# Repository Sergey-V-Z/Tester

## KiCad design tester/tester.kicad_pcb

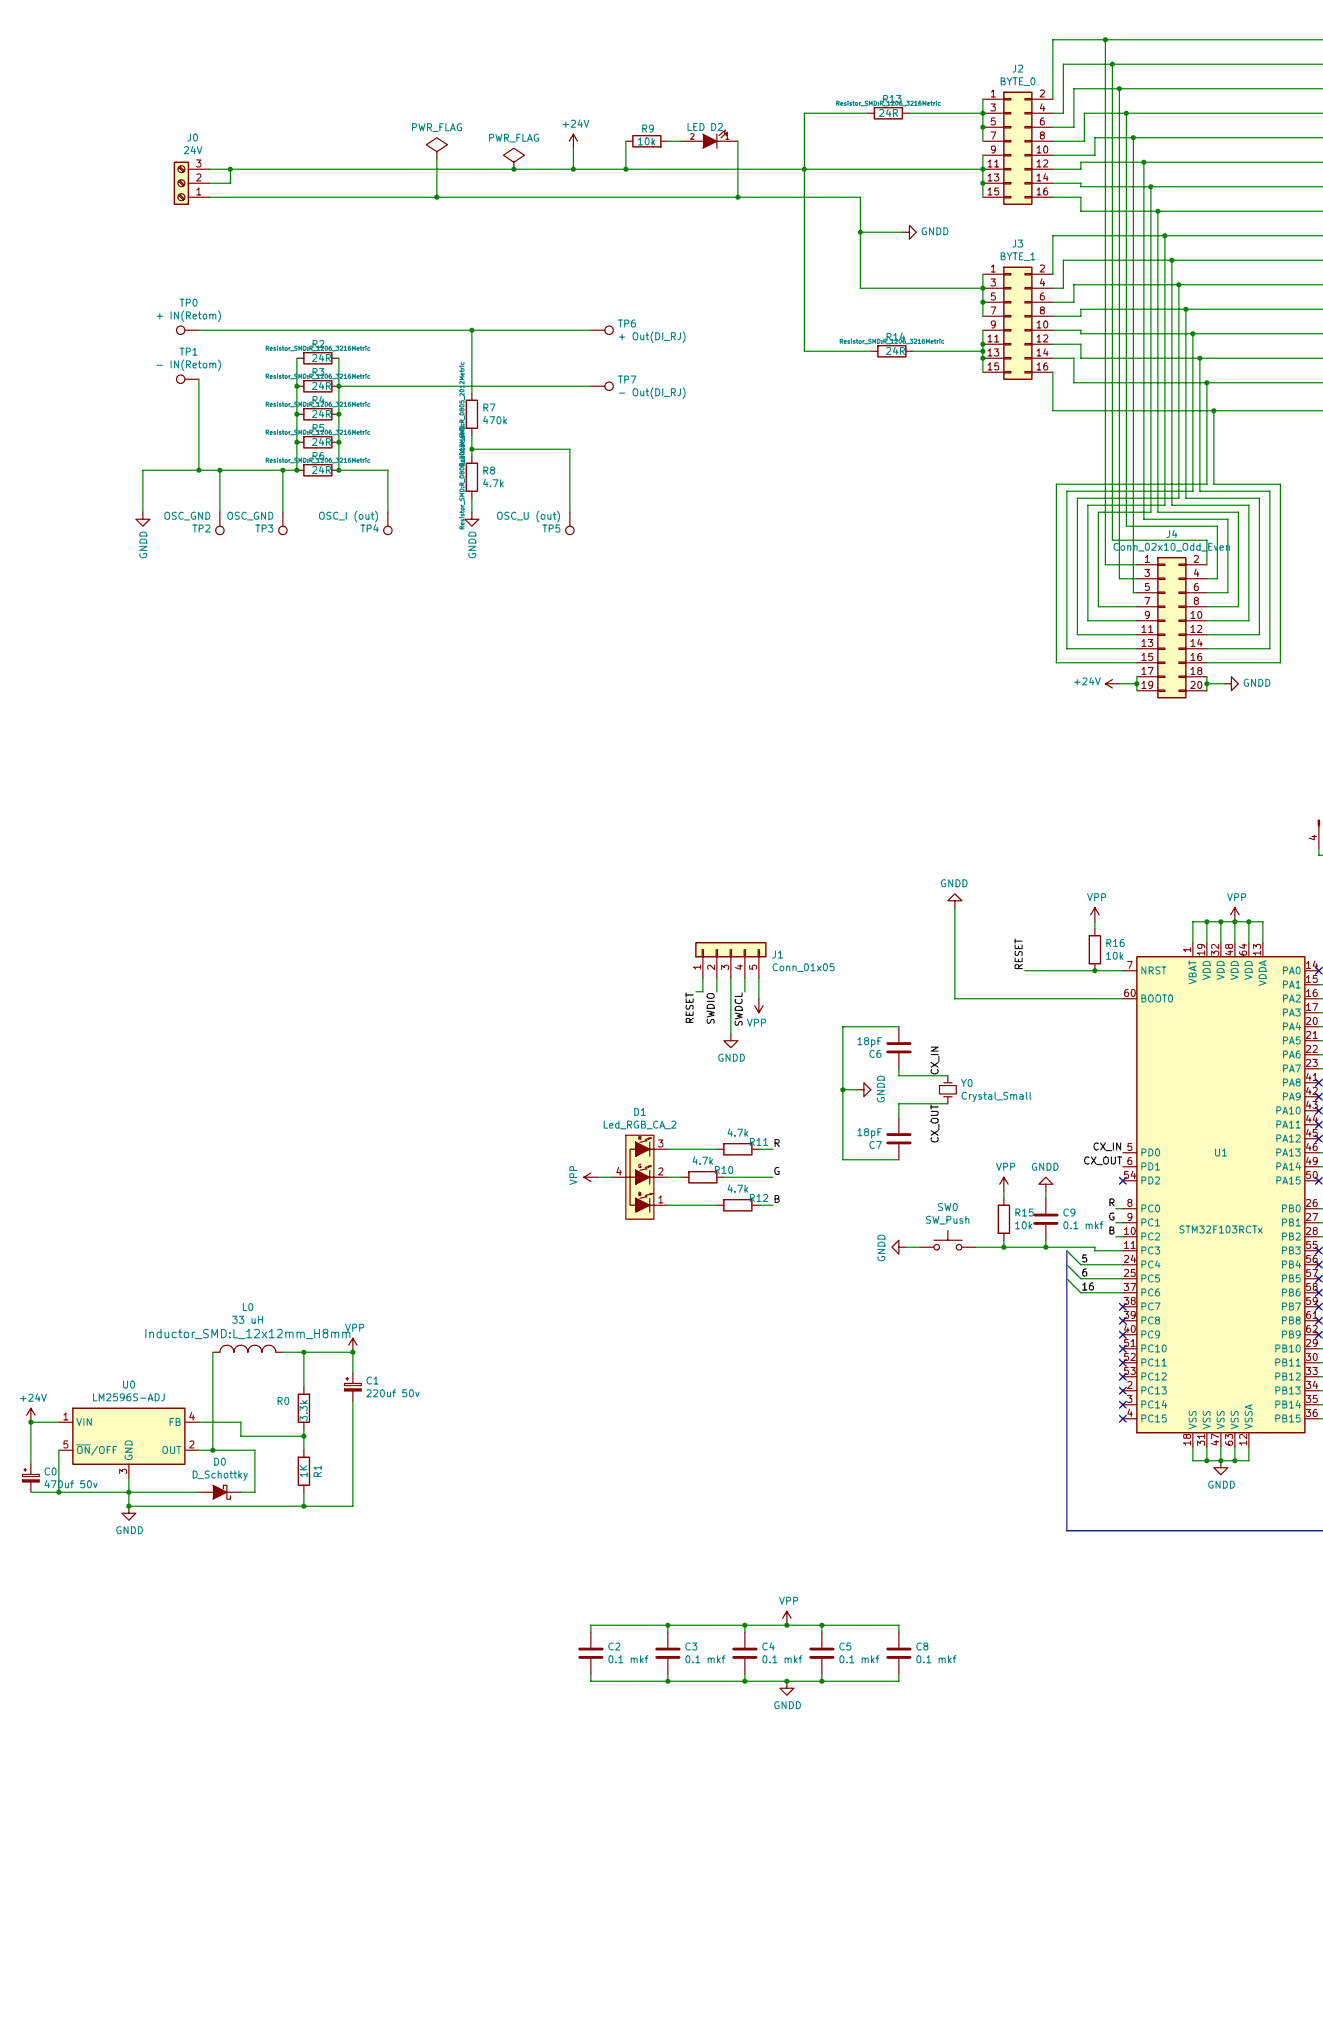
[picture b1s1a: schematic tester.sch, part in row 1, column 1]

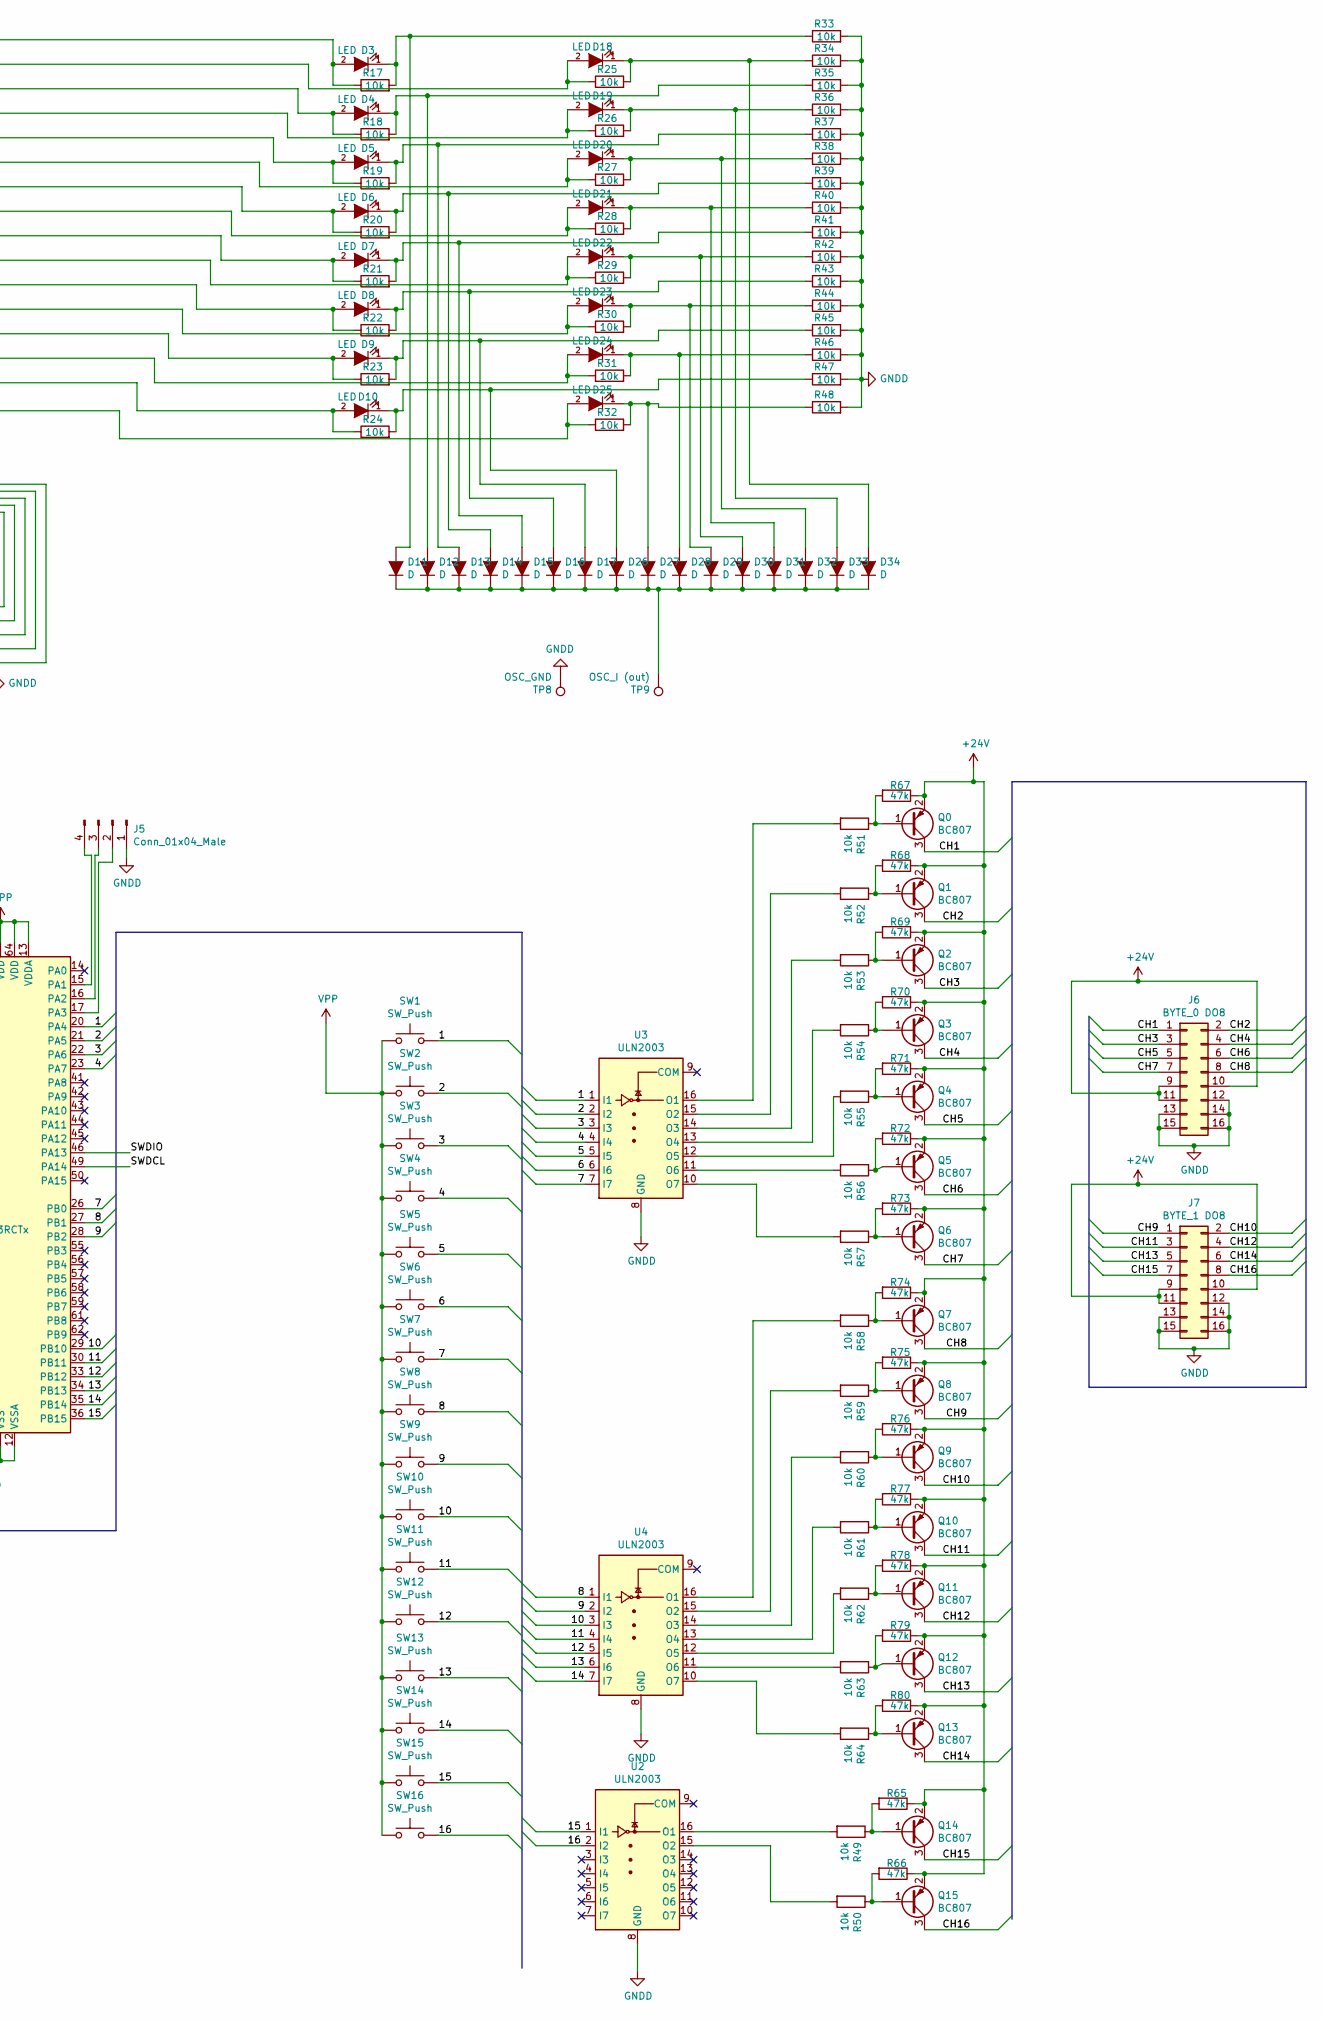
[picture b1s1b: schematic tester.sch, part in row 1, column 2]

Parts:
C0: 470uf 50v; CP_Radial_D10.0mm_P5.00mm
C1: 220uf 50v; CP_Radial_D10.0mm_P5.00mm
C2, C3, C4, C5, C8, C9: 0.1 mkf; C_0603_1608Metric_Pad1.05x0.95mm_HandSolder
C6, C7: 18pF; C_0603_1608Metric
D0: D_Schottky; D_SMC
D1: Led_RGB_CA_2; LED_Avago_PLCC4_3.2x2.8mm_CW
D2, D3, D4, D5, D6, D7, D8, D9, D10, D18, D19, D20, D21, D22, D23, D24, D25: LED; D_0805_2012Metric
D11, D12, D13, D14, D15, D16, D17, D26, D27, D28, D29, D30, D31, D32, D33, D34: D; D_SMB_Handsoldering
J0: 24V; TerminalBlock_bornier-3_P5.08mm
J1: Conn_01x05; PinHeader_1x05_P2.54mm_Vertical
J2: BYTE_0; IDC-Header_2x08_P2.54mm_Vertical
J3: BYTE_1; IDC-Header_2x08_P2.54mm_Vertical
J4: Conn_02x10_Odd_Even; IDC-Header_2x10_P2.54mm_Vertical
J5: Conn_01x04_Male; PinSocket_1x04_P2.54mm_Vertical
J6: BYTE_0 DO8; IDC-Header_2x08_P2.54mm_Vertical
J7: BYTE_1 DO8; IDC-Header_2x08_P2.54mm_Vertical
L0: 33 uH; L_12x12mm_H8mm
Q0, Q1, Q2, Q3, Q4, Q5, Q6, Q7, Q8, Q9, Q10, Q11, Q12, Q13, Q14, Q15: BC807; SOT-23
R0: 3.3k; R_0805_2012Metric_Pad1.15x1.40mm_HandSolder
R1: 1K; R_0805_2012Metric
R2, R3, R4, R5, R6, R13, R14: 24R; R_1206_3216Metric
R7: 470k; R_0805_2012Metric
R8: 4.7k; R_0805_2012Metric
R9, R17, R18, R19, R20, R21, R22, R23, R24, R25, R26, R27, R28, R29, R30, R31, R32, R33, R34, R35, R36, R37, R38, R39, R40, R41, R42, R43, R44, R45, R46, R47, R48: 10k; R_0805_2012Metric
R10, R11, R12: 4.7k; R_0805_2012Metric_Pad1.15x1.40mm_HandSolder
R15, R16, R49, R50, R51, R52, R53, R54, R55, R56, R57, R58, R59, R60, R61, R62, R63, R64: 10k; R_0805_2012Metric_Pad1.15x1.40mm_HandSolder
R65, R66, R67, R68, R69, R70, R71, R72, R73, R74, R75, R76, R77, R78, R79, R80: 47k; R_0805_2012Metric_Pad1.15x1.40mm_HandSolder
SW0, SW1, SW2, SW3, SW4, SW5, SW6, SW7, SW8, SW9, SW10, SW11, SW12, SW13, SW14, SW15, SW16: SW_Push; SW_PUSH_6mm
TP0: + IN(Retom); TestPoint_Plated_Hole_D3.0mm
TP1: - IN(Retom); TestPoint_Plated_Hole_D3.0mm
TP2, TP3, TP8: OSC_GND; TestPoint_Loop_D2.60mm_Drill0.9mm_Beaded
TP4, TP9: OSC_I (out); TestPoint_Loop_D2.60mm_Drill0.9mm_Beaded
TP5: OSC_U (out); TestPoint_Loop_D2.60mm_Drill0.9mm_Beaded
TP6: + Out(DI_RJ); TestPoint_Plated_Hole_D3.0mm
TP7: - Out(DI_RJ); TestPoint_Plated_Hole_D3.0mm
U0: LM2596S-ADJ; TO-263-5_TabPin3
U1: STM32F103RCTx; LQFP-64_10x10mm_P0.5mm
U2, U3, U4: ULN2003; SOIC-16_3.9x9.9mm_P1.27mm
Y0: Crystal_Small; Crystal_SMD_HC49-SD

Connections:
+24V: C0.1, J0.2, J0.3, J2.9, J2.11, J2.13, J2.15, J4.17, J4.19, J6.9, J6.10, J6.11, J7.9, J7.10, J7.11, Q0.2 (E), Q1.2 (E), Q2.2 (E), Q3.2 (E), Q4.2 (E), Q5.2 (E), Q6.2 (E), Q7.2 (E), Q8.2 (E), Q9.2 (E), Q10.2 (E), Q11.2 (E), Q12.2 (E), Q13.2 (E), Q14.2 (E), Q15.2 (E), R9.1, R13.2, R14.2, R65.1, R66.1, R67.1, R68.1, R69.1, R70.1, R71.1, R72.1, R73.1, R74.1, R75.1, R76.1, R77.1, R78.1, R79.1, R80.1, U0.1 (VIN)
/1: SW1.2, U1.20 (PA4), U3.1 (I1)
/2: SW2.2, U1.21 (PA5), U3.2 (I2)
/3: SW3.2, U1.22 (PA6), U3.3 (I3)
/4: SW4.2, U1.23 (PA7), U3.4 (I4)
/5: SW5.2, U1.24 (PC4), U3.5 (I5)
/6: SW6.2, U1.25 (PC5), U3.6 (I6)
/7: SW7.2, U1.26 (PB0), U3.7 (I7)
/8: SW8.2, U1.27 (PB1), U4.1 (I1)
/9: SW9.2, U1.28 (PB2), U4.2 (I2)
/10: SW10.2, U1.29 (PB10), U4.3 (I3)
/11: SW11.2, U1.30 (PB11), U4.4 (I4)
/12: SW12.2, U1.33 (PB12), U4.5 (I5)
/13: SW13.2, U1.34 (PB13), U4.6 (I6)
/14: SW14.2, U1.35 (PB14), U4.7 (I7)
/15: SW15.2, U1.36 (PB15), U2.1 (I1)
/16: SW16.2, U1.37 (PC6), U2.2 (I2)
/B: R12.1, U1.10 (PC2)
/CH1: J6.1, Q0.3 (C)
/CH2: J6.2, Q1.3 (C)
/CH3: J6.3, Q2.3 (C)
/CH4: J6.4, Q3.3 (C)
/CH5: J6.5, Q4.3 (C)
/CH6: J6.6, Q5.3 (C)
/CH7: J6.7, Q6.3 (C)
/CH8: J6.8, Q7.3 (C)
/CH9: J7.1, Q8.3 (C)
/CH10: J7.2, Q9.3 (C)
/CH11: J7.3, Q10.3 (C)
/CH12: J7.4, Q11.3 (C)
/CH13: J7.5, Q12.3 (C)
/CH14: J7.6, Q13.3 (C)
/CH15: J7.7, Q14.3 (C)
/CH16: J7.8, Q15.3 (C)
/CX_IN: C6.1, U1.5 (PD0), Y0.1
/CX_OUT: C7.2, U1.6 (PD1), Y0.2
/G: R10.1, U1.9 (PC1)
/R: R11.1, U1.8 (PC0)
/RESET: J1.1, R16.2, U1.7 (NRST)
/SWDCL: J1.4, U1.49 (PA14)
/SWDIO: J1.2, U1.46 (PA13)
GNDD: C0.2, C1.2, C2.2, C3.2, C4.2, C5.2, C6.2, C7.1, C8.2, C9.1, D0.2 (A), D2.1 (K), J0.1, J1.3, J3.1, J3.3, J3.5, J3.7, J4.18, J4.20, J5.1, J6.12, J6.13, J6.14, J6.15, J6.16, J7.12, J7.13, J7.14, J7.15, J7.16, R1.1, R2.2, R3.2, R4.2, R5.2, R6.2, R8.2, R33.2, R34.2, R35.2, R36.2, R37.2, R38.2, R39.2, R40.2, R41.2, R42.2, R43.2, R44.2, R45.2, R46.2, R47.2, R48.2, SW0.1, TP1.1, TP2.1, TP3.1, TP8.1, U0.3 (GND), U0.5 (~ON~/OFF), U1.12 (VSSA), U1.18 (VSS), U1.31 (VSS), U1.47 (VSS), U1.60 (BOOT0), U1.63 (VSS), U2.8 (GND), U3.8 (GND), U4.8 (GND)
unnamed: C9.2, R15.2, SW0.2, U1.11 (PC3)
unnamed: D0.1 (K), L0.1, U0.2 (OUT)
unnamed: D1.1 (B), R12.2
unnamed: D1.2 (G), R10.2
unnamed: D1.3 (R), R11.2
unnamed: D2.2 (A), R9.2
unnamed: D3.2 (A), J2.2, J4.1, R17.1
unnamed: D4.2 (A), J2.6, J4.3, R18.1
unnamed: D5.2 (A), J2.10, J4.5, R19.1
unnamed: D6.2 (A), J2.14, J4.7, R20.1
unnamed: D7.2 (A), J3.2, J4.9, R21.1
unnamed: D8.2 (A), J3.6, J4.11, R22.1
unnamed: D9.2 (A), J3.10, J4.13, R23.1
unnamed: D10.1 (K), D26.2 (A), R24.2, R47.1
unnamed: D10.2 (A), J3.14, J4.15, R24.1
unnamed: D11.1 (K), D12.1 (K), D13.1 (K), D14.1 (K), D15.1 (K), D16.1 (K), D17.1 (K), D26.1 (K), D27.1 (K), D28.1 (K), D29.1 (K), D30.1 (K), D31.1 (K), D32.1 (K), D33.1 (K), D34.1 (K), TP9.1
unnamed: D3.1 (K), D11.2 (A), R17.2, R33.1
unnamed: D4.1 (K), D12.2 (A), R18.2, R35.1
unnamed: D5.1 (K), D13.2 (A), R19.2, R37.1
unnamed: D6.1 (K), D14.2 (A), R20.2, R39.1
unnamed: D7.1 (K), D15.2 (A), R21.2, R41.1
unnamed: D8.1 (K), D16.2 (A), R22.2, R43.1
unnamed: D9.1 (K), D17.2 (A), R23.2, R45.1
unnamed: D18.1 (K), D34.2 (A), R25.2, R34.1
unnamed: D18.2 (A), J2.4, J4.2, R25.1
unnamed: D19.1 (K), D33.2 (A), R26.2, R36.1
unnamed: D19.2 (A), J2.8, J4.4, R26.1
unnamed: D20.1 (K), D32.2 (A), R27.2, R38.1
unnamed: D20.2 (A), J2.12, J4.6, R27.1
unnamed: D21.1 (K), D31.2 (A), R28.2, R40.1
unnamed: D21.2 (A), J2.16, J4.8, R28.1
unnamed: D22.1 (K), D30.2 (A), R29.2, R42.1
unnamed: D22.2 (A), J3.4, J4.10, R29.1
unnamed: D23.1 (K), D29.2 (A), R30.2, R44.1
unnamed: D23.2 (A), J3.8, J4.12, R30.1
unnamed: D24.1 (K), D28.2 (A), R31.2, R46.1
unnamed: D24.2 (A), J3.12, J4.14, R31.1
unnamed: D25.1 (K), D27.2 (A), R32.2, R48.1
unnamed: D25.2 (A), J3.16, J4.16, R32.1
unnamed: J2.1, J2.3, J2.5, J2.7, R13.1
unnamed: J3.9, J3.11, J3.13, J3.15, R14.1
unnamed: J5.2, U1.17 (PA3)
unnamed: J5.3, U1.16 (PA2)
unnamed: J5.4, U1.15 (PA1)
unnamed: Q0.1 (B), R51.1, R67.2
unnamed: Q1.1 (B), R52.1, R68.2
unnamed: Q2.1 (B), R53.1, R69.2
unnamed: Q3.1 (B), R54.1, R70.2
unnamed: Q4.1 (B), R55.1, R71.2
unnamed: Q5.1 (B), R56.1, R72.2
unnamed: Q6.1 (B), R57.1, R73.2
unnamed: Q7.1 (B), R58.1, R74.2
unnamed: Q8.1 (B), R59.1, R75.2
unnamed: Q9.1 (B), R60.1, R76.2
unnamed: Q10.1 (B), R61.1, R77.2
unnamed: Q11.1 (B), R62.1, R78.2
unnamed: Q12.1 (B), R63.1, R79.2
unnamed: Q13.1 (B), R64.1, R80.2
unnamed: Q14.1 (B), R49.1, R65.2
unnamed: Q15.1 (B), R50.1, R66.2
unnamed: R0.1, R1.2, U0.4 (FB)
unnamed: R2.1, R3.1, R4.1, R5.1, R6.1, TP4.1, TP7.1
unnamed: R7.1, TP0.1, TP6.1
unnamed: R7.2, R8.1, TP5.1
unnamed: R49.2, U2.16 (O1)
unnamed: R50.2, U2.15 (O2)
unnamed: R51.2, U3.16 (O1)
unnamed: R52.2, U3.15 (O2)
unnamed: R53.2, U3.14 (O3)
unnamed: R54.2, U3.13 (O4)
unnamed: R55.2, U3.12 (O5)
unnamed: R56.2, U3.11 (O6)
unnamed: R57.2, U3.10 (O7)
unnamed: R58.2, U4.16 (O1)
unnamed: R59.2, U4.15 (O2)
unnamed: R60.2, U4.14 (O3)
unnamed: R61.2, U4.13 (O4)
unnamed: R62.2, U4.12 (O5)
unnamed: R63.2, U4.11 (O6)
unnamed: R64.2, U4.10 (O7)
VPP: C1.1, C2.1, C3.1, C4.1, C5.1, C8.1, D1.4, J1.5, L0.2, R0.2, R15.1, R16.1, SW1.1, SW2.1, SW3.1, SW4.1, SW5.1, SW6.1, SW7.1, SW8.1, SW9.1, SW10.1, SW11.1, SW12.1, SW13.1, SW14.1, SW15.1, SW16.1, U1.1 (VBAT), U1.13 (VDDA), U1.19 (VDD), U1.32 (VDD), U1.48 (VDD), U1.64 (VDD)

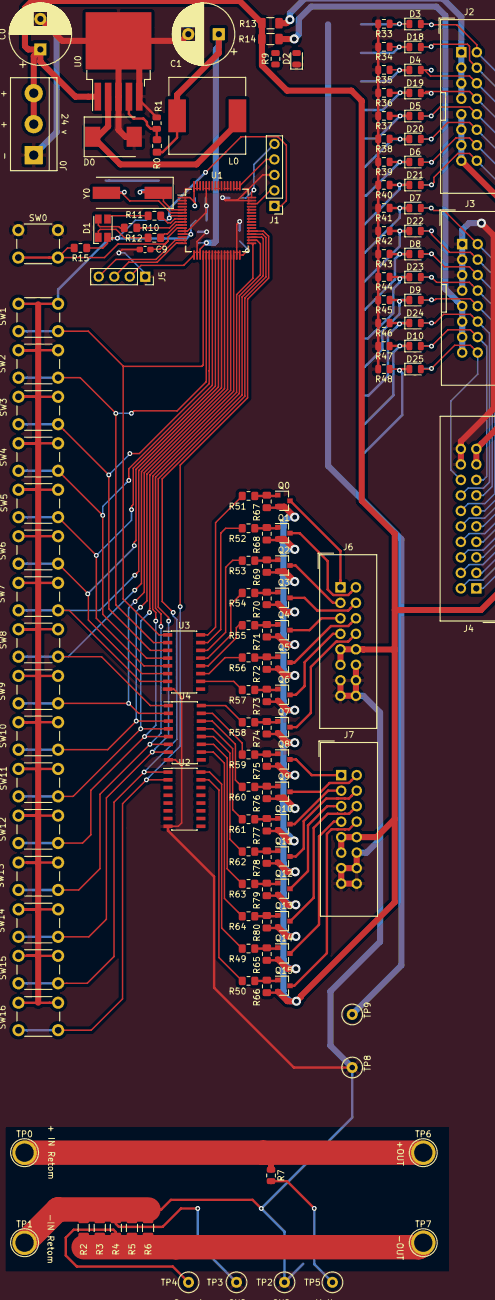
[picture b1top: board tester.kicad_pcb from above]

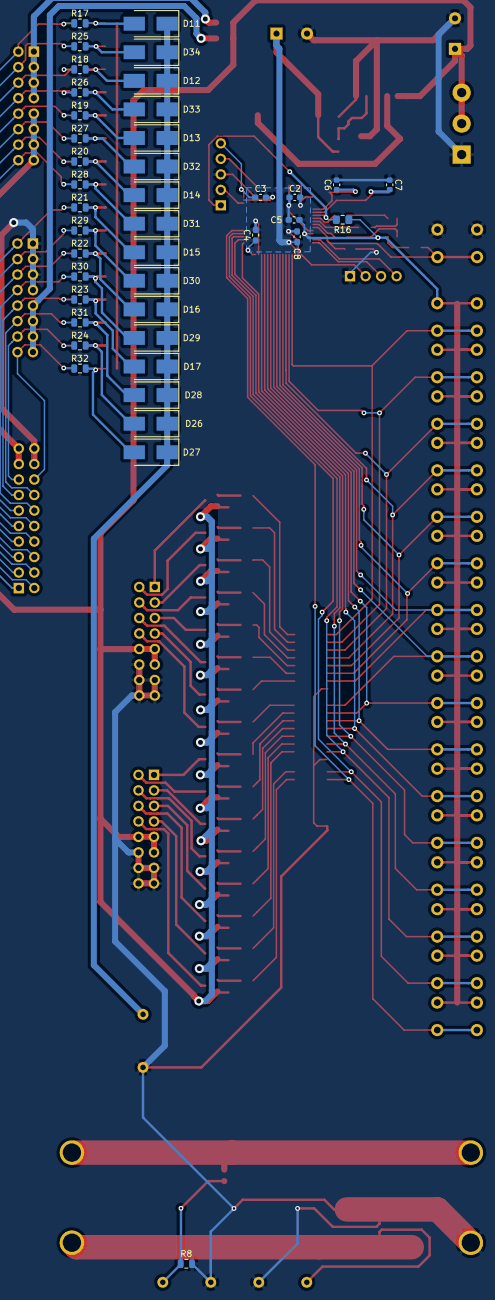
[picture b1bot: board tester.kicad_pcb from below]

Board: 2 copper layers, 184 parts (41 on the bottom side), 123 nets.

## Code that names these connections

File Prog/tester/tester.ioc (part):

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Mcu.Name=STM32F103R(C-D-E)Tx
Mcu.Package=LQFP64
Mcu.UserName=STM32F103RCTx
PA1.Signal=GPIO_Output
PA13.Mode=Serial_Wire
PA13.Signal=SYS_JTMS-SWDIO
PA14.Mode=Serial_Wire
PA14.Signal=SYS_JTCK-SWCLK
PA2.Mode=Asynchronous
PA2.Signal=USART2_TX
PA3.Mode=Asynchronous
PA3.Signal=USART2_RX
PA4.Signal=GPIO_Output
PA5.Signal=GPIO_Output
PA6.Signal=GPIO_Output
PA7.Signal=GPIO_Output
PB0.Signal=GPIO_Output
PB1.Signal=GPIO_Output
PB10.Signal=GPIO_Output
PB11.Signal=GPIO_Output
PB12.Signal=GPIO_Output
PB13.Signal=GPIO_Output
PB14.Signal=GPIO_Output
PB15.Signal=GPIO_Output
PB2.Signal=GPIO_Output
PC4.Signal=GPIO_Output
PC5.Signal=GPIO_Output
PC6.Signal=GPIO_Output
PD0-OSC_IN.Mode=HSE-External-Oscillator
PD0-OSC_IN.Signal=RCC_OSC_IN
PD1-OSC_OUT.Mode=HSE-External-Oscillator
PD1-OSC_OUT.Signal=RCC_OSC_OUT
RCC.SYSCLKFreq_VALUE=72000000
RCC.SYSCLKSource=RCC_SYSCLKSOURCE_PLLCLK
board=custom

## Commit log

2020-08-16 Finish
    First finish
